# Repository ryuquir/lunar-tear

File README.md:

# Lunar Tear

Private server research project for a certain discontinued mobile game.
Discord server: https://discord.gg/G3anrfcV

## How To Launch The Server

### Prerequisites

- Go 1.24+
- Populated `server/assets/` directory

### Regenerate protobuf stubs

```bash
cd server
make proto
```

### Run

```bash
cd server
sudo go run ./cmd/lunar-tear \
  --host 10.0.2.2 \
  --http-port 8080 \
  --scene 13
```

`sudo` is needed because gRPC binds to port 443 (privileged). On Linux you can use `setcap` instead:

```bash
go build -o lunar-tear ./cmd/lunar-tear
sudo setcap cap_net_bind_service=+ep ./lunar-tear
./lunar-tear --host 10.0.2.2 --http-port 8080 --scene 13
```

### Ports

| Protocol | Port | Notes                                                |
| -------- | ---- | ---------------------------------------------------- |
| gRPC     | 443  | hardcoded by the client, not configurable            |
| HTTP     | 8080 | Octo asset API + game web pages (`--http-port` flag) |

### Flags

| Flag                   | Default             | Description                                              |
| ---------------------- | ------------------- | -------------------------------------------------------- |
| `--host`               | `127.0.0.1`         | hostname/IP given to the client                          |
| `--http-port`          | `8080`              | HTTP/Octo server port                                    |
| `--resources-base-url` | (derived from host) | base URL for list.bin rewrite (must be exactly 43 chars) |
| `--scene`              | `0`                 | bootstrap new users to scene N (0 = fresh start)         |

### `--resources-base-url`

Overrides the base URL the client uses to fetch resources. The replacement string **must be exactly 43 characters**. If omitted, the server derives it from `--host` and `--http-port` automatically (when the result happens to be 43 characters). If the length doesn't match, the server logs a warning and serves the resource list unchanged.

```bash
sudo go run ./cmd/lunar-tear \
  --host 10.0.2.2 \
  --http-port 8080 \
  --resources-base-url "http://192.168.1.50:8080/res-bundle-srv" \
  --scene 13
```

> **Tip:** verify the length with `printf "your-url-here" | wc -c`.

## ⚠️ Legal Disclaimer

**Lunar Tear** is a fan-made, non-commercial **preservation and research project** dedicated to keeping a certain discontinued mobile game playable for educational and archival purposes.

- This project is **not affiliated with**, **endorsed by**, or **approved by** the original publisher or any of its subsidiaries.
- All trademarks, copyrights, and intellectual property related to the original game and its associated franchises belong to their respective owners.
- All code in this repository is original work developed through clean-room reverse engineering for interoperability with the game client.
- No copyrighted game assets, binaries, or master data are distributed in this repository.

**Use at your own risk.** The author assumes no liability for any damages or legal consequences that may arise from using this software. By using or contributing to this project, you are solely responsible for ensuring your usage complies with all applicable laws in your jurisdiction.

This project is released under the [MIT License](LICENSE).

**If you are a rights holder with concerns regarding this project**, please contact me directly.

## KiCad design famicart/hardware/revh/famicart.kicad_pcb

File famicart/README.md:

# famicart — RP2040/RP2350 ファミコン・マルチマッパー・カートリッジ ファームウェア＋基板

ファミコン（NES）の公式・ライセンス品 2,233 タイトルで使われた 92 種のマッパーを調査し、その全種（タイトル数ベース **99.0%**（2,211 本）。残り 22 本はデータベース上の不良ダンプ）に加え、基板名の記録がない市販 FC ソフト用のマッパーも含めて計 98 種をソフトウェアで再現する 1 チップ・カートリッジのファームウェアです。フラッシュに書き込んだ ROM 画像からマッパーを自動判別し、プロファイル指定で「MMC5 のバンク機能 + VRC7 音源」のような拡張 IC の組み合わせも可能にします。

> **重要な前提**: Seeed Studio XIAO RP2040 は GPIO が 11 本しかなく、単体ではカートリッジバス（最低 26 本）を駆動できません。理由と数値は [docs/01_feasibility.md](docs/01_feasibility.md) を参照。そのため **rev C 基板では基板直付けの RP2350B（GPIO 48 本）がバスを担当し、XIAO RP2040 は拡張音源コプロセッサ**として同居します（[docs/04_hardware.md](docs/04_hardware.md) の rev C 節）。rev A/B は Pico / Pico 2 モジュール 1 個の構成です。

## 状態（フェーズ 1・2 完了、フェーズ 3 = 実機検証 待ち）

| 項目 | 状態 |
|---|---|
| マッパー調査・集計（Mesen DB 由来） | 完了 → [docs/03_mapper_coverage.md](docs/03_mapper_coverage.md) |
| コア（バンク表・マッパー 99 種〔ライセンス品の 98 種＋自作向けのマッパー 30（UNROM 512、フラッシュ自己書き込み対応）〕・ROM 判別・DB 2,840 件・プロファイル） | 実装済み、ホストテスト 2,122 チェック通過 |
| 拡張音源レジスタ・ルーター（組み合わせ機構） | 実装済み |
| 拡張音源の合成（VRC6/VRC7/MMC5/N163/5B/FDS、`src/core/audio/synth.c`） | 実装済み（6 音源とも発音をホストテストで確認、VRC7 は OPLL 近似）。rev C では XIAO 側で動作 |
| PIO バス・フロントエンド、2 コア処理、PWM 音声出力 | 実装済み・**実機未検証** |
| USB-CDC コマンド（INFO / RESET / BOOTSEL / LOAD / PROFILE）と転送ツール `tools/fcload.py` | 実装済み・**実機未検証** |
| Pico / Pico 2 / RP2350B / XIAO（コプロセッサ）向けビルド | 通過（Pico: text 120KB, BSS 249KB / RP2350B: text 106KB, BSS 512KB / XIAO audio: text 42KB） |
| 2 MCU 間 UART リンク（3 Mbaud、音源レジスタのストリーム） | 実装済み・**実機未検証** |
| 回路図・基板 rev B（Pico 2、KiCad 7、90×46.1 mm〔※外形は旧寸法で切り欠きなし＝基板単体用。[04](docs/04_hardware.md) の訂正を参照〕、USB-C・リセット付き、未接続 0・DRC 0）・ガーバー・JLCPCB 実装パッケージ | [hardware/](hardware/)、[hardware/jlcpcb/](hardware/jlcpcb/) |
| 回路図・基板 rev C（RP2350B + XIAO RP2040、USB 3 口、リセット端子 J2、未接続 0・DRC 0）・ガーバー・JLCPCB 実装パッケージ | [hardware/revc/](hardware/revc/) |
| 回路図・基板 rev D（**実機動作の本命**: 実カセット型分離構成、RP2350B×2 マッパーチップ + PRG/CHR パラレル NOR 64 MB×2 + F-RAM 128 KB + CHR SRAM 512 KB、**6 層、未接続 0・DRC エラー 0**、起動バンク付き）・ガーバー・JLCPCB 実装パッケージ | [hardware/revd/](hardware/revd/)、[hardware/revd/jlcpcb/](hardware/revd/jlcpcb/)、docs/04_hardware.md の rev D 節 |
| 回路図・基板 rev E（※外形は旧寸法で切り欠きなし＝基板単体用。標準シェルには Pico 2 が 1 枚しか入らないため rev E は標準シェル不可、[04 の訂正](docs/04_hardware.md)）（**実際に作れる安価な版**: Pico 2 ×2 + XIAO RP2350、JLCPCB Basic 部品のみ 10 種・45 点、2 層、未接続 0・DRC エラー 0、MMC5 完全対応の配線）・ガーバー・JLCPCB 実装パッケージ | [hardware/reve/](hardware/reve/)、[docs/06_rev_e_plan.md](docs/06_rev_e_plan.md) |
| 回路図・基板 **rev F2**（rev F の回路を**任天堂の大型シェル**に合わせ、4 資料から作った外形〔切り欠き・スリット・リブ回避。実物では未確認〕で配置、90 × 85.7 mm、Pico 2 ×4 + XIAO、Basic 部品のみ 10 種・54 点、2 層、**未接続 0・DRC エラー 0**） | [hardware/revf2/](hardware/revf2/)、[docs/10_rev_f_board.md](docs/10_rev_f_board.md) |
| 回路図・基板 **rev G**（Pico 2 ×2 ＋ XIAO RP2350 ×2 を基本に、増設 Pico 2 ×2〔512 KB 級の PRG・CHR 用、任意〕、16 MB フラッシュ、microSD〔任意〕。任天堂の大型シェル用 89.6 × 85.7 mm、2 層、Basic 部品のみ 10 種・81 点、**未接続 0・DRC エラー 0**。外形・ビア・シルク・端子部を JLCPCB の製造条件に合わせ、Standard PCBA 用の注文パッケージ（捨て基板を描き込んだデータと、基板だけのデータ）を付けた。検査ツールが 2 つのガーバー ZIP の中身と捨て基板の寸法をデータから測る。設計レビューで見つかった回路の問題〔書き込みストローブ、/ROMSEL、PPU /WE、31 番端子、PPU データ線の直列抵抗など〕を修正。**実機とシェルの実物では未検証、rev G 用のファームは未作成**） | [hardware/revg/](hardware/revg/)（[外形図](hardware/revg/outline.png)、[配置図](hardware/revg/placement.png)、[注文メモ](hardware/revg/jlcpcb/README.md)）、[docs/12_rev_g_plan.md](docs/12_rev_g_plan.md)、ファミコン本体の仕様と全端子は [docs/11_famicom_reference.md](docs/11_famicom_reference.md) |
| 回路図・基板 **rev H**（rev G の 6 つのモジュールを RP2350B 6 個の直接実装に置き換え、計算専用の RP2350B 2 個を足した計 8 個。**JLCPCB の実装だけで完成**する rev G の上位互換。各チップに 16 MB フラッシュ、チップ間の高速リンク、共通のコア電源、6 層・両面実装（表は受動部品だけ）・25 種 296 点、ファミコンの電源だけで動かすための電流の決まり。任天堂の大型シェル用、線幅と間隔 0.12 mm、**未接続 0・DRC エラー 0**、JLCPCB の注文パッケージと GrokBOT 用の注文手順付き。**ファームは未作成**） | [hardware/revh/](hardware/revh/)、[docs/13_rev_h_plan.md](docs/13_rev_h_plan.md) |
| 回路図・基板 rev F（rev E + SFC 型コプロセッサ用 Pico 2 ×2、90 × 70.1 mm、Basic 部品のみ 10 種・54 点、2 層、**未接続 0・DRC エラー 0**。外形は旧寸法で切り欠きなし＝基板単体用） | [hardware/revf/](hardware/revf/)、[docs/10_rev_f_board.md](docs/10_rev_f_board.md)、コプロセッサ ABI は [docs/09_coproc_abi.md](docs/09_coproc_abi.md) |
| rev E ファームウェア（U1 CPU バス応答・書き込み取り込み・CHR-RAM 再現・起動手順・ROM ライブラリ、U2 CHR/CIRAM /CE・MMC5 PPU 処理、U3 IRQ・拡張音源、3 台リンク） | 実装済み・3 本ともビルド通過、ホストテスト通過（rev E 分 52 項目、追加マッパー 524 項目）、**実機未検証**。[docs/07_rev_e_firmware.md](docs/07_rev_e_firmware.md) |
| rev D ファームウェア（バンク線出力、2 MCU リンク、外部フラッシュ書き込み、ROM ライブラリ、ブートスタブ） | 実装済み・ビルド通過（U1 text 130 KB / U2 37 KB）、ホストテスト通過、**実機未検証** |

## ビルド

```sh
# ホスト側ユニットテスト
cd famicart/test && make

# ファームウェア（FC_BOARD = pico | pico2 | rp2350b | xiao_audio | xiao_rp2040）
cd famicart && mkdir -p build && cd build
cmake -DPICO_SDK_PATH=/path/to/pico-sdk -DFC_BOARD=pico2 ..
make -j
# -> famicart.uf2 を BOOTSEL モードのドライブへコピー

# rev C 基板は 2 つ書く: 主 MCU（J3 を挿し SW2 を押しながら SW1 を離す）と XIAO（XIAO 自身の USB-C と BOOT ボタン）
cmake -S . -B build-rp2350b   -DFC_BOARD=rp2350b   && cmake --build build-rp2350b   # -> RP2350B へ
cmake -S . -B build-xiao_audio -DFC_BOARD=xiao_audio && cmake --build build-xiao_audio # -> XIAO RP2040 へ

# rev H の待機用プログラム（チップごと。FC_REVH_CHIP = 1〜6・8・9、6 はハブ。docs/13 の「ファームの土台」）
cmake -S . -B build-revh_u6 -DFC_BOARD=revh -DFC_REVH_CHIP=6 && cmake --build build-revh_u6   # ピンのヘッダーの確認: python3 tools/fw/gen_revh_pins.py --check
```

## ROM の書き込み（自動判別）

```sh
# そのまま: ヘッダ → CRC32 DB → サイズ推定 の順で自動判別
python3 tools/rom2uf2.py game.nes -o game.uf2 --family rp2350

# マッパーを強制し、VRC7 音源を追加（MMC5 の機能 + VRC7 の音）
python3 tools/rom2uf2.py game.nes -o game.uf2 --mapper 5 --audio vrc7:exclusive --audio mmc5

# レジスタ窓が衝突する組み合わせは窓を移動（VRC6 のレジスタを $C000 へ）
python3 tools/rom2uf2.py game.nes -o game.uf2 --audio vrc6@0xC000
```

## 本体に挿したまま ROM を転送（USB-C）

```sh
pip install pyserial
python3 tools/fcload.py /dev/ttyACM0 info          # 判別結果・バス統計
python3 tools/fcload.py /dev/ttyACM0 load game.nes # 転送 → カートリッジ自動再起動 → 本体のリセットを押す
python3 tools/fcload.py /dev/ttyACM0 reset         # ソフトからカートリッジをリセット
python3 tools/fcload.py /dev/ttyACM0 bootsel       # ファーム更新用 UF2 モードへ
```

ROM はフラッシュ先頭から 256KB の位置（`FC_FLASH_ROM_SLOT`）に、48 バイトのプロファイル（256 バイト境界にパディング）＋画像の形で書き込まれます。ツールを介さず `.nes` を直接その位置に焼いた場合もヘッダ/DB で判別します。起動後、USB CDC（115200）に判別結果とバス統計が 2 秒ごとに出ます。

## データベースの再生成

```sh
python3 tools/gen_romdb.py   # data/MesenNesDB.txt -> src/core/romdb_gen.h, docs/03_mapper_coverage.md
```

## ドキュメント

- [01 実現可能性](docs/01_feasibility.md) — ピン数・タイミング・メモリの数値と結論
- [02 ファームウェア構成](docs/02_architecture.md) — 高速パス、マッパー IF、音源ルーター、判別フロー、既知の制約
- [03 マッパー集計](docs/03_mapper_coverage.md) — 92 種の本数・サブマッパー・代表基板・実装状況
- [04 ハードウェア](docs/04_hardware.md) — KiCad プロジェクト、基板寸法、GPIO 割当、部品表、音声ミックス回路

## 基板の再生成（KiCad 7 + Freerouting）

```sh
cd famicart/tools/pcb
python3 gen_sch.py && python3 route_pcb.py && python3 gen_bom.py && python3 gen_jlc.py            # rev B -> hardware/
FC_DESIGN=design_revc FC_HW_DIR=../../hardware/revc python3 gen_sch.py   # rev C -> hardware/revc/（route_pcb / gen_bom / gen_jlc も同じ環境変数で）
FC_DESIGN=design_revd FC_HW_DIR=../../hardware/revd FC_LAYERS=6 FC_STUBS=1 FC_TRACK=0.1 FC_CLEAR=0.1 FC_VIA=0.5 FC_VIA_DRILL=0.2 python3 route_pcb.py   # rev D（6 層）
python3 finish_route.py ../../hardware/revd/famicart.kicad_pcb   # Freerouting が残した接続を仕上げる（その後 route_pcb.py export）
```

## ロードマップ

1. **フェーズ 3**: 基板の試作・実機検証（ロジアナでタイミング確認）、配線の手直し、VRC7 音色の実機比較による校正、USB マスストレージからの ROM 選択、セーブ（バッテリ RAM）のフラッシュ退避
2. **フェーズ 4（rev D 向けファーム）**: 実装済み（バンク出力・リンク・フラッシュ書き込み・ライブラリ・ブートスタブ）。残り: 起動メニュー（コントローラでライブラリ選択）、MMC5 $5204 状態の U2→U1 同期、$6000 PRG-ROM マッパーの F-RAM コピー対応
3. **フェーズ 5（実機ブリングアップ）**: 基板到着後 `FLASHID` → `BOOTBANK` → `libadd` NROM → MMC1 → MMC3 → MMC5 の順に確認。ロジアナで M2 ↔ バンク線・/RD ↔ CHR バンク線の遅延を測る
4. 未実装マッパー（海賊版マルチカート系）は対象外のまま

## ライセンス・出典

ファームウェアはリポジトリのライセンスに従います。`data/MesenNesDB.txt` は Mesen プロジェクト配布の生成データ（NesCartDB および NewRisingSun の NES 2.0 header database 由来）で、マッパー判別用のメタデータのみを利用しています。ゲーム ROM は含みません。

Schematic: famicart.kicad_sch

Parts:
C1, C2, C5, C6, C7, C9, C10, C11, C12, C13, C14, C16, C17, C18, C21, C22, C23, C24, C25, C26, C27, C28, C29, C30, C31, C33, C34, C35, C38, C39, C40, C41, C42, C43, C44, C45, C46, C47, C48, C50, C51, C52, C55, C56, C57, C58, C59, C60, C61, C62, C63, C64, C65, C67, C68, C69, C72, C73, C74, C75, C76, C77, C78, C79, C80, C81, C82, C84, C85, C86, C89, C90, C91, C92, C93, C94, C95, C96, C97, C98, C99, C101, C102, C103, C106, C107, C108, C109, C110, C111, C112, C113, C114, C115, C116, C118, C119, C120, C123, C124, C125, C126, C127, C128, C129, C130, C131, C132, C133, C135, C136, C137, C148: 100n; C_0402_1005Metric
C3, C4, C8, C142, C145, C146: 10u; C_0805_2012Metric
C15, C32, C49, C66, C83, C100, C117, C134, C147: 4.7u; C_0603_1608Metric
C19, C20, C36, C37, C53, C54, C70, C71, C87, C88, C104, C105, C121, C122, C138, C139: 12p; C_0402_1005Metric
C140, C141: 10n; C_0603_1608Metric
C143, C144: 22u; C_0805_2012Metric
D5, D6, D7, D8, D9: BAV99; SOT-23
D10, D11: B5819W; D_SOD-123
D21, D22, D23, D24, D25, D26, D28, D29: KT-0603R; LED_0603_1608Metric
J1: Famicom 60-pin edge; Famicom_CardEdge_60_M
J2: RST/GND/LINK pads; WirePads_1x3
J3: TF-01A; microSD_HRO_TF-01A
J4: EXT/GND/3V3 pads; WirePads_1x3
J5: hub SWD pads; PinHeader_1x05_P1.27mm_Vertical_SMD_Pin1Left
J6: SWD pads U1-U5 U8 U9; PinHeader_2x08_P1.27mm_Vertical_SMD
J7: TYPE-C-31-M-12; USB_C_Receptacle_HRO_TYPE-C-31-M-12_JLC
L1, L2: 2.2uH; L_SXN_SMNR4020
Q1, Q2, Q3, Q4, Q5, Q6, Q7: 2N7002; SOT-23
R1, R3, R5, R7, R9, R11, R13, R15, R52: 1k; R_0402_1005Metric
R2, R4, R6, R8, R10, R12, R14, R16, R17, R19, R20, R21, R22, R23, R24, R28, R29, R32, R37, R51, R54: 2.2k; R_0603_1608Metric
R18, R33, R34, R35, R46, R48, R49, R50: 100k; R_0603_1608Metric
R25, R26, R27, R30, R31, R36, R40, R41, R42, R43, R44, R45, R47, R53: 10k; R_0603_1608Metric
R38, R39: 27; R_0402_1005Metric
RN1, RN2, RN3, RN4, RN7, RN8, RN9, RN10, RN17, RN18, RN19, RN20, RN21, RN22, RN23, RN24, RN25, RN26, RN31, RN32: 1k x4; R_Array_Convex_4x0603
RN5, RN6, RN11, RN12, RN13, RN14, RN15, RN16, RN27, RN28, RN29, RN30: 680 x4; R_Array_Convex_4x0603
SW1: TS-1187A (RESET); SW_Push_1P1T_XKB_TS-1187A
SW2: TS-1187A (BOOTSEL); SW_Push_1P1T_XKB_TS-1187A
SW3: TS-1187A (HUB RUN); SW_Push_1P1T_XKB_TS-1187A
TP1: TP +1V1; TestPoint_Pad_1.5x1.5mm
TP2: TP +3V3; TestPoint_Pad_1.5x1.5mm
TP3: TP V5_IN; TestPoint_Pad_1.5x1.5mm
TP4: TP FB_3V3; TestPoint_Pad_1.5x1.5mm
TP5: TP FB_1V1; TestPoint_Pad_1.5x1.5mm
TP6: TP GND; TestPoint_Pad_1.5x1.5mm
U1, U2, U3, U4, U5, U6, U8, U9: RP2350B; QFN-80-1EP_10x10mm_P0.4mm_EP3.4x3.4mm_NoVia
U7, U11, U12, U13, U14, U15, U16, U18, U19: W25Q128JVSIQ; SOIC-8_5.23x5.23mm_P1.27mm
U20, U21: TLV62569DBVR; SOT-23-5
Y1, Y2, Y3, Y4, Y5, Y6, Y8, Y9: 12MHz; Crystal_SMD_3225-4Pin_3.2x2.5mm
ZA1, ZA2, ZA3, ZA4: 1k x4; R_Array_Convex_4x0603
ZD1, ZD2: 680 x4; R_Array_Convex_4x0603

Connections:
+1V1: C5.1, C10.1, C18.1, C23.1, C27.1, C35.1, C40.1, C44.1, C52.1, C57.1, C61.1, C69.1, C74.1, C78.1, C86.1, C91.1, C95.1, C103.1, C108.1, C112.1, C120.1, C125.1, C129.1, C137.1, C143.1, C144.1, L2.2, R30.1, TP1.1, U1.10 (DVDD), U1.32 (DVDD), U1.51 (DVDD), U2.10 (DVDD), U2.32 (DVDD), U2.51 (DVDD), U3.10 (DVDD), U3.32 (DVDD), U3.51 (DVDD), U4.10 (DVDD), U4.32 (DVDD), U4.51 (DVDD), U5.10 (DVDD), U5.32 (DVDD), U5.51 (DVDD), U6.10 (DVDD), U6.32 (DVDD), U6.51 (DVDD), U8.10 (DVDD), U8.32 (DVDD), U8.51 (DVDD), U9.10 (DVDD), U9.32 (DVDD), U9.51 (DVDD)
+3V3: C1.1, C2.1, C6.1, C7.1, C9.1, C11.1, C12.1, C13.1, C14.1, C15.1, C16.1, C17.1, C21.1, C22.1, C24.1, C25.1, C26.1, C28.1, C29.1, C30.1, C31.1, C32.1, C33.1, C34.1, C38.1, C39.1, C41.1, C42.1, C43.1, C45.1, C46.1, C47.1, C48.1, C49.1, C50.1, C51.1, C55.1, C56.1, C58.1, C59.1, C60.1, C62.1, C63.1, C64.1, C65.1, C66.1, C67.1, C68.1, C72.1, C73.1, C75.1, C76.1, C77.1, C79.1, C80.1, C81.1, C82.1, C83.1, C84.1, C85.1, C89.1, C90.1, C92.1, C93.1, C94.1, C96.1, C97.1, C98.1, C99.1, C100.1, C101.1, C102.1, C106.1, C107.1, C109.1, C110.1, C111.1, C113.1, C114.1, C115.1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
+5V: C3.1, C4.1, C8.1, D5.2 (A), D6.2 (A), D7.2 (A), D8.2 (A), D9.2 (A), D10.2 (A), J1.30 (+5V), J1.31 (CART_PRESENT), R17.2, R18.2, R26.1, RN18.5 (R4.2)
AF1: C140.1, RN19.3 (R3.1), RN19.5 (R4.2), RN19.8 (R1.2)
AF2: C141.1, RN19.2 (R2.1), RN19.6 (R3.2)
AMIX: R19.2, R20.1
AUDIO_IN: J1.45 (AUDIO_IN), R19.1
AUDIO_OUT: J1.46 (AUDIO_OUT), R20.2, RN19.7 (R2.2)
BOOT6: R52.2, SW2.1
CA0: RN1.8 (R1.2), U1.77 (GPIO0), U4.77 (GPIO0)
CA1: RN1.7 (R2.2), U1.78 (GPIO1), U4.78 (GPIO1)
CA2: RN1.6 (R3.2), U1.79 (GPIO2), U4.79 (GPIO2)
CA3: RN1.5 (R4.2), U1.80 (GPIO3), U4.80 (GPIO3)
CA4: RN2.8 (R1.2), U1.1 (GPIO4), U4.1 (GPIO4)
CA5: RN2.7 (R2.2), U1.2 (GPIO5), U4.2 (GPIO5)
CA6: RN2.6 (R3.2), U1.3 (GPIO6), U4.3 (GPIO6)
CA7: RN2.5 (R4.2), U1.4 (GPIO7), U4.4 (GPIO7)
CA8: RN3.8 (R1.2), U1.6 (GPIO8), U4.6 (GPIO8)
CA9: RN3.7 (R2.2), U1.7 (GPIO9), U4.7 (GPIO9)
CA10: RN3.6 (R3.2), U1.8 (GPIO10), U4.8 (GPIO10)
CA11: RN3.5 (R4.2), U1.9 (GPIO11), U4.9 (GPIO11)
CA12: RN4.6 (R3.2), U1.11 (GPIO12), U4.11 (GPIO12)
CA13: RN4.7 (R2.2), U1.12 (GPIO13), U4.12 (GPIO13)
CA14: RN4.8 (R1.2), U1.13 (GPIO14), U4.13 (GPIO14)
CC1: J7.A5 (CC1), R42.1, R43.1
CC2: J7.B5 (CC2), R40.1, R41.1
CD0: RN5.8 (R1.2), U1.14 (GPIO15)
CD1: RN5.7 (R2.2), U1.16 (GPIO16)
CD2: RN5.6 (R3.2), U1.17 (GPIO17)
CD3: RN5.5 (R4.2), U1.18 (GPIO18)
CD4: RN6.8 (R1.2), U1.19 (GPIO19)
CD5: RN6.7 (R2.2), U1.20 (GPIO20)
CD6: RN6.6 (R3.2), U1.21 (GPIO21)
CD7: RN6.5 (R4.2), U1.22 (GPIO22)
CIRAM_A10: J1.18 (CIRAM_A10), RN17.1 (R1.1), RN17.2 (R2.1)
CIRAM_nCE: J1.48 (CIRAM_~CE), R25.1, RN7.3 (R3.1), RN7.4 (R4.1)
CPU_A0: J1.13 (CPU_A0), RN1.1 (R1.1), ZA1.1 (R1.1)
CPU_A1: J1.12 (CPU_A1), RN1.2 (R2.1), ZA1.2 (R2.1)
CPU_A2: J1.11 (CPU_A2), RN1.3 (R3.1), ZA1.3 (R3.1)
CPU_A3: J1.10 (CPU_A3), RN1.4 (R4.1), ZA1.4 (R4.1)
CPU_A4: J1.9 (CPU_A4), RN2.1 (R1.1), ZA2.1 (R1.1)
CPU_A5: J1.8 (CPU_A5), RN2.2 (R2.1), ZA2.2 (R2.1)
CPU_A6: J1.7 (CPU_A6), RN2.3 (R3.1), ZA2.3 (R3.1)
CPU_A7: J1.6 (CPU_A7), RN2.4 (R4.1), ZA2.4 (R4.1)
CPU_A8: J1.5 (CPU_A8), RN3.1 (R1.1), ZA3.1 (R1.1)
CPU_A9: J1.4 (CPU_A9), RN3.2 (R2.1), ZA3.2 (R2.1)
CPU_A10: J1.3 (CPU_A10), RN3.3 (R3.1), ZA3.3 (R3.1)
CPU_A11: J1.2 (CPU_A11), RN3.4 (R4.1), ZA3.4 (R4.1)
CPU_A12: J1.33 (CPU_A12), RN4.3 (R3.1), ZA4.3 (R3.1)
CPU_A13: J1.34 (CPU_A13), RN4.2 (R2.1), ZA4.2 (R2.1)
CPU_A14: J1.35 (CPU_A14), RN4.1 (R1.1), ZA4.1 (R1.1)
CPU_D0: J1.43 (CPU_D0), RN5.1 (R1.1), RN13.1 (R1.1), ZD1.1 (R1.1)
CPU_D1: J1.42 (CPU_D1), RN5.2 (R2.1), RN13.2 (R2.1), ZD1.2 (R2.1)
CPU_D2: J1.41 (CPU_D2), RN5.3 (R3.1), RN13.3 (R3.1), ZD1.3 (R3.1)
CPU_D3: J1.40 (CPU_D3), RN5.4 (R4.1), RN13.4 (R4.1), ZD1.4 (R4.1)
CPU_D4: J1.39 (CPU_D4), RN6.1 (R1.1), RN14.1 (R1.1), ZD2.1 (R1.1)
CPU_D5: J1.38 (CPU_D5), RN6.2 (R2.1), RN14.2 (R2.1), ZD2.2 (R2.1)
CPU_D6: J1.37 (CPU_D6), RN6.3 (R3.1), RN14.3 (R3.1), ZD2.3 (R3.1)
CPU_D7: J1.36 (CPU_D7), RN6.4 (R4.1), RN14.4 (R4.1), ZD2.4 (R4.1)
CPU_RW: D6.3 (K), J1.14 (CPU_R/~W), Q2.1 (G), R18.1, RN31.2 (R2.1), RN31.4 (R4.1)
C_M2: RN4.5 (R4.2), U1.25 (GPIO24), U4.25 (GPIO24)
C_ROMSEL: RN31.6 (R3.2), U1.26 (GPIO25), U4.26 (GPIO25)
C_RW: RN31.5 (R4.2), U1.23 (GPIO23), U4.23 (GPIO23)
EXT: R54.2, U6.52 (GPIO41_ADC1)
EXT_P: J4.1, R54.1
FB_1V1: R30.2, R31.1, R33.1, TP5.1, U21.5 (FB)
FB_1V1_M: R31.2, R32.1
FB_3V3: R36.2, R37.1, TP4.1, U20.5 (FB)
GND: C1.2, C2.2, C3.2, C4.2, C5.2, C6.2, C7.2, C8.2, C9.2, C10.2, C11.2, C12.2, C13.2, C14.2, C15.2, C16.2, C17.2, C18.2, C19.2, C20.2, C21.2, C22.2, C23.2, C24.2, C25.2, C26.2, C27.2, C28.2, C29.2, C30.2, C31.2, C32.2, C33.2, C34.2, C35.2, C36.2, C37.2, C38.2, C39.2, C40.2, C41.2, C42.2, C43.2, C44.2, C45.2, C46.2, C47.2, C48.2, C49.2, C50.2, C51.2, C52.2, C53.2, C54.2, C55.2, C56.2, C57.2, C58.2, C59.2, C60.2, C61.2, C62.2, C63.2, C64.2, C65.2, C66.2, C67.2, C68.2, C69.2, C70.2, C71.2, C72.2, C73.2, C74.2, C75.2, C76.2, C77.2, C78.2, C79.2, C80.2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
HIRQ: U3.39 (GPIO31), U6.40 (GPIO32)
HM2: RN18.8 (R1.2), U6.42 (GPIO33)
IRQ4: U3.53 (GPIO42_ADC2), U4.55 (GPIO44_ADC4)
IRQ5: U3.54 (GPIO43_ADC3), U5.55 (GPIO44_ADC4)
IRQ_G: Q5.1 (G), R21.1, U3.38 (GPIO30)
LED1: R8.1, U1.58 (GPIO47_ADC7)
LED1_A: D21.2 (A), R8.2
LED2: R4.1, U2.56 (GPIO45_ADC5)
LED2_A: D22.2 (A), R4.2
LED3: R6.1, U3.56 (GPIO45_ADC5)
LED3_A: D23.2 (A), R6.2
LED4: R16.1, U4.57 (GPIO46_ADC6)
LED4_A: D24.2 (A), R16.2
LED5: R12.1, U5.57 (GPIO46_ADC6)
LED5_A: D25.2 (A), R12.2
LED6: R14.1, U6.48 (GPIO39)
LED6_A: D26.2 (A), R14.2
LED8: R10.1, U8.56 (GPIO45_ADC5)
LED8_A: D28.2 (A), R10.2
LED9: R2.1, U9.56 (GPIO45_ADC5)
LED9_A: D29.2 (A), R2.2
LINK: R22.1, R24.1, RN20.5 (R4.2), RN20.6 (R3.2), RN20.7 (R2.2), RN20.8 (R1.2), RN21.5 (R4.2), RN21.6 (R3.2), RN21.7 (R2.2), RN21.8 (R1.2), RN22.5 (R4.2), RN22.6 (R3.2), RN22.7 (R2.2), RN22.8 (R1.2), RN23.5 (R4.2), RN23.6 (R3.2), RN23.7 (R2.2), RN23.8 (R1.2), RN24.5 (R4.2), RN24.6 (R3.2), RN24.7 (R2.2), RN24.8 (R1.2), RN25.5 (R4.2), RN25.6 (R3.2), RN25.7 (R2.2), RN25.8 (R1.2)
LINK_A: RN20.1 (R1.1), RN20.2 (R2.1), RN20.3 (R3.1), RN20.4 (R4.1), U1.36 (GPIO28)
LINK_B: RN22.1 (R1.1), RN22.2 (R2.1), RN22.3 (R3.1), RN22.4 (R4.1), U2.36 (GPIO28)
LINK_C: RN24.1 (R1.1), RN24.2 (R2.1), RN24.3 (R3.1), RN24.4 (R4.1), U3.36 (GPIO28)
LINK_D: RN21.1 (R1.1), RN21.2 (R2.1), RN21.3 (R3.1), RN21.4 (R4.1), U4.36 (GPIO28)
LINK_E: RN23.1 (R1.1), RN23.2 (R2.1), RN23.3 (R3.1), RN23.4 (R4.1), U5.36 (GPIO28)
LINK_F: RN25.1 (R1.1), RN25.2 (R2.1), RN25.3 (R3.1), RN25.4 (R4.1), U6.77 (GPIO0)
LINK_PU: R22.2, R23.1
LINK_T: J2.3, R24.2
M2: D5.3 (K), J1.32 (M2), Q1.1 (G), RN4.4 (R4.1), RN18.1 (R1.1), ZA4.4 (R4.1)
M2n: Q1.3 (D), Q3.1 (G), RN18.4 (R4.1)
NA10_D: RN17.7 (R2.2), RN17.8 (R1.2), U3.47 (GPIO38)
NCE_D: RN7.5 (R4.2), RN7.6 (R3.2), U3.46 (GPIO37)
PA0: RN10.6 (R3.2), U2.77 (GPIO0), U5.77 (GPIO0)
PA1: RN9.8 (R1.2), U2.78 (GPIO1), U5.78 (GPIO1)
PA2: RN9.6 (R3.2), U2.79 (GPIO2), U5.79 (GPIO2)
PA3: RN8.8 (R1.2), U2.80 (GPIO3), U5.80 (GPIO3)
PA4: RN8.6 (R3.2), U2.1 (GPIO4), U5.1 (GPIO4)
PA5: RN7.8 (R1.2), U2.2 (GPIO5), U5.2 (GPIO5)
PA6: RN7.7 (R2.2), U2.3 (GPIO6), U5.3 (GPIO6)
PA7: RN8.5 (R4.2), U2.4 (GPIO7), U5.4 (GPIO7)
PA8: RN8.7 (R2.2), U2.6 (GPIO8), U5.6 (GPIO8)
PA9: RN9.5 (R4.2), U2.7 (GPIO9), U5.7 (GPIO9)
PA10: RN9.7 (R2.2), U2.8 (GPIO10), U3.40 (GPIO32), U5.8 (GPIO10)
PA11: RN10.5 (R4.2), U2.9 (GPIO11), U3.42 (GPIO33), U5.9 (GPIO11)
PA12: RN10.7 (R2.2), U2.11 (GPIO12), U3.43 (GPIO34), U5.11 (GPIO12)
PA13: RN10.8 (R1.2), U2.12 (GPIO13), U3.44 (GPIO35), U5.12 (GPIO13)
PD0: RN11.5 (R4.2), RN11.6 (R3.2), U2.13 (GPIO14)
PD1: RN11.7 (R2.2), RN11.8 (R1.2), U2.14 (GPIO15)
PD2: RN12.5 (R4.2), RN12.6 (R3.2), U2.16 (GPIO16)
PD3: RN12.7 (R2.2), RN12.8 (R1.2), U2.17 (GPIO17)
PD4: RN16.5 (R4.2), RN16.6 (R3.2), U2.18 (GPIO18)
PD5: RN16.7 (R2.2), RN16.8 (R1.2), U2.19 (GPIO19)
PD6: RN15.5 (R4.2), RN15.6 (R3.2), U2.20 (GPIO20)
PD7: RN15.7 (R2.2), RN15.8 (R1.2), U2.21 (GPIO21)
PEV: U2.23 (GPIO23), U3.48 (GPIO39)
PLINK_B: RN26.7 (R2.2), RN26.8 (R1.2), U2.28 (GPIO27)
PLINK_E: RN26.5 (R4.2), RN26.6 (R3.2), U5.28 (GPIO27)
PLINK_F: RN26.1 (R1.1), RN26.2 (R2.1), RN26.3 (R3.1), RN26.4 (R4.1), U6.17 (GPIO17)
PPU_A0: J1.25 (PPU_A0), RN10.3 (R3.1)
PPU_A1: J1.24 (PPU_A1), RN9.1 (R1.1)
PPU_A2: J1.23 (PPU_A2), RN9.3 (R3.1)
PPU_A3: J1.22 (PPU_A3), RN8.1 (R1.1)
PPU_A4: J1.21 (PPU_A4), RN8.3 (R3.1)
PPU_A5: J1.20 (PPU_A5), RN7.1 (R1.1)
PPU_A6: J1.19 (PPU_A6), RN7.2 (R2.1)
PPU_A7: J1.50 (PPU_A7), RN8.4 (R4.1)
PPU_A8: J1.51 (PPU_A8), RN8.2 (R2.1)
PPU_A9: J1.52 (PPU_A9), RN9.4 (R4.1)
PPU_A10: J1.53 (PPU_A10), RN9.2 (R2.1)
PPU_A11: J1.54 (PPU_A11), RN10.4 (R4.1)
PPU_A12: J1.55 (PPU_A12), RN10.2 (R2.1)
PPU_A13: J1.56 (PPU_A13), RN10.1 (R1.1)
PPU_D0: J1.26 (PPU_D0), RN11.3 (R3.1), RN11.4 (R4.1), RN27.1 (R1.1), RN27.2 (R2.1)
PPU_D1: J1.27 (PPU_D1), RN11.1 (R1.1), RN11.2 (R2.1), RN27.3 (R3.1), RN27.4 (R4.1)
PPU_D2: J1.28 (PPU_D2), RN12.3 (R3.1), RN12.4 (R4.1), RN28.1 (R1.1), RN28.2 (R2.1)
PPU_D3: J1.29 (PPU_D3), RN12.1 (R1.1), RN12.2 (R2.1), RN28.3 (R3.1), RN28.4 (R4.1)
PPU_D4: J1.60 (PPU_D4), RN16.3 (R3.1), RN16.4 (R4.1), RN30.1 (R1.1), RN30.2 (R2.1)
PPU_D5: J1.59 (PPU_D5), RN16.1 (R1.1), RN16.2 (R2.1), RN30.3 (R3.1), RN30.4 (R4.1)
PPU_D6: J1.58 (PPU_D6), RN15.3 (R3.1), RN15.4 (R4.1), RN29.1 (R1.1), RN29.2 (R2.1)
PPU_D7: J1.57 (PPU_D7), RN15.1 (R1.1), RN15.2 (R2.1), RN29.3 (R3.1), RN29.4 (R4.1)
PPU_nRD: J1.17 (PPU_~RD), RN17.4 (R4.1), RN32.3 (R3.1)
PPU_nWE: J1.47 (PPU_~WR), RN17.3 (R3.1), RN32.4 (R4.1)
PWE_G: D9.3 (K), Q6.1 (G), RN17.6 (R3.2)
PWM: RN19.4 (R4.1), U3.37 (GPIO29)
PWM2: RN19.1 (R1.1), U6.43 (GPIO34)
PWS_D: Q6.3 (D), R28.1, R29.1, U2.27 (GPIO26), U5.27 (GPIO26)
P_WE: RN32.5 (R4.2), U2.25 (GPIO24), U5.25 (GPIO24)
QSPI1_SCLK: U1.71 (QSPI_SCLK), U11.6 (CLK)
QSPI1_SD0: U1.72 (QSPI_SD0), U11.5 (DI(IO0))
QSPI1_SD1: U1.74 (QSPI_SD1), U11.2 (DO(IO1))
QSPI1_SD2: U1.73 (QSPI_SD2), U11.3 (IO2)
QSPI1_SD3: U1.70 (QSPI_SD3), U11.7 (IO3)
QSPI1_SS: U1.75 (QSPI_SS), U11.1 (~CS)
QSPI2_SCLK: U2.71 (QSPI_SCLK), U12.6 (CLK)
QSPI2_SD0: U2.72 (QSPI_SD0), U12.5 (DI(IO0))
QSPI2_SD1: U2.74 (QSPI_SD1), U12.2 (DO(IO1))
QSPI2_SD2: U2.73 (QSPI_SD2), U12.3 (IO2)
QSPI2_SD3: U2.70 (QSPI_SD3), U12.7 (IO3)
QSPI2_SS: U2.75 (QSPI_SS), U12.1 (~CS)
QSPI3_SCLK: U3.71 (QSPI_SCLK), U13.6 (CLK)
QSPI3_SD0: U3.72 (QSPI_SD0), U13.5 (DI(IO0))
QSPI3_SD1: U3.74 (QSPI_SD1), U13.2 (DO(IO1))
QSPI3_SD2: U3.73 (QSPI_SD2), U13.3 (IO2)
QSPI3_SD3: U3.70 (QSPI_SD3), U13.7 (IO3)
QSPI3_SS: U3.75 (QSPI_SS), U13.1 (~CS)
QSPI4_SCLK: U4.71 (QSPI_SCLK), U14.6 (CLK)
QSPI4_SD0: U4.72 (QSPI_SD0), U14.5 (DI(IO0))
QSPI4_SD1: U4.74 (QSPI_SD1), U14.2 (DO(IO1))
QSPI4_SD2: U4.73 (QSPI_SD2), U14.3 (IO2)
QSPI4_SD3: U4.70 (QSPI_SD3), U14.7 (IO3)
QSPI4_SS: U4.75 (QSPI_SS), U14.1 (~CS)
QSPI5_SCLK: U5.71 (QSPI_SCLK), U15.6 (CLK)
QSPI5_SD0: U5.72 (QSPI_SD0), U15.5 (DI(IO0))
QSPI5_SD1: U5.74 (QSPI_SD1), U15.2 (DO(IO1))
QSPI5_SD2: U5.73 (QSPI_SD2), U15.3 (IO2)
QSPI5_SD3: U5.70 (QSPI_SD3), U15.7 (IO3)
QSPI5_SS: U5.75 (QSPI_SS), U15.1 (~CS)
QSPI6_SCLK: U6.71 (QSPI_SCLK), U7.6 (CLK), U16.6 (CLK)
QSPI6_SD0: U6.72 (QSPI_SD0), U7.5 (DI(IO0)), U16.5 (DI(IO0))
QSPI6_SD1: U6.74 (QSPI_SD1), U7.2 (DO(IO1)), U16.2 (DO(IO1))
QSPI6_SD2: U6.73 (QSPI_SD2), U7.3 (IO2), U16.3 (IO2)
QSPI6_SD3: U6.70 (QSPI_SD3), U7.7 (IO3), U16.7 (IO3)
QSPI6_SS: R52.1, U6.75 (QSPI_SS), U16.1 (~CS)
QSPI6_SS1: R51.1, U6.58 (GPIO47_ADC7), U7.1 (~CS)
QSPI8_SCLK: U8.71 (QSPI_SCLK), U18.6 (CLK)
QSPI8_SD0: U8.72 (QSPI_SD0), U18.5 (DI(IO0))
QSPI8_SD1: U8.74 (QSPI_SD1), U18.2 (DO(IO1))
QSPI8_SD2: U8.73 (QSPI_SD2), U18.3 (IO2)
QSPI8_SD3: U8.70 (QSPI_SD3), U18.7 (IO3)
QSPI8_SS: U8.75 (QSPI_SS), U18.1 (~CS)
QSPI9_SCLK: U9.71 (QSPI_SCLK), U19.6 (CLK)
QSPI9_SD0: U9.72 (QSPI_SD0), U19.5 (DI(IO0))
QSPI9_SD1: U9.74 (QSPI_SD1), U19.2 (DO(IO1))
QSPI9_SD2: U9.73 (QSPI_SD2), U19.3 (IO2)
QSPI9_SD3: U9.70 (QSPI_SD3), U19.7 (IO3)
QSPI9_SS: U9.75 (QSPI_SS), U19.1 (~CS)
RD_D: RN17.5 (R4.2), U2.22 (GPIO22), U5.22 (GPIO22)
RD_D3: RN32.6 (R3.2), U3.45 (GPIO36)
RSEL_D: Q4.3 (D), RN18.2 (R2.1), U1.27 (GPIO26), U4.27 (GPIO26)
RUN6: J5.3, SW3.1, U6.35 (RUN)
SD_CD: J3.9 (DET), U6.78 (GPIO1)
SD_CLK: J3.5 (CLK), U6.79 (GPIO2)
SD_CMD: J3.3 (CMD), R48.1, U6.80 (GPIO3)
SD_DAT0: J3.7 (DAT0), R49.1, U6.1 (GPIO4)
SD_DAT1: J3.8 (DAT1), R50.1, U6.2 (GPIO5)
SD_DAT2: J3.1 (DAT2), R46.1, U6.3 (GPIO6)
SD_DAT3: J3.2 (DAT3/CD), R47.1, U6.4 (GPIO7)
SWCLK1: J6.1, U1.33 (SWCLK), U6.46 (GPIO37)
SWCLK2: J6.3, U2.33 (SWCLK), U6.20 (GPIO20)
SWCLK3: J6.5, U3.33 (SWCLK), U6.22 (GPIO22)
SWCLK4: J6.7, U4.33 (SWCLK), U6.44 (GPIO35)
SWCLK5: J6.9, U5.33 (SWCLK), U6.18 (GPIO18)
SWCLK6: J5.1, U6.33 (SWCLK)
SWCLK8: J6.11, U6.54 (GPIO43_ADC3), U8.33 (SWCLK)
SWCLK9: J6.13, U6.56 (GPIO45_ADC5), U9.33 (SWCLK)
SWDIO1: J6.2, U1.34 (SWDIO), U6.47 (GPIO38)
SWDIO2: J6.4, U2.34 (SWDIO), U6.21 (GPIO21)
SWDIO3: J6.6, U3.34 (SWDIO), U6.23 (GPIO23)
SWDIO4: J6.8, U4.34 (SWDIO), U6.45 (GPIO36)
SWDIO5: J6.10, U5.34 (SWDIO), U6.19 (GPIO19)
SWDIO6: J5.2, U6.34 (SWDIO)
SWDIO8: J6.12, U6.55 (GPIO44_ADC4), U8.34 (SWDIO)
SWDIO9: J6.14, U6.57 (GPIO46_ADC6), U9.34 (SWDIO)
SW_1V1: L2.1, U21.3 (SW)
SW_3V3: L1.1, U20.3 (SW)
USB_DM: J7.A7 (D-), J7.B7 (D-), R39.2
USB_DM_R: R39.1, U6.66 (USB_DM)
USB_DP: J7.A6 (D+), J7.B6 (D+), R38.2
USB_DP_R: R38.1, U6.67 (USB_DP)
V5S: R26.2, R27.1, U6.49 (GPIO40_ADC0)
V5_IN: C142.1, C145.1, D10.1 (K), D11.1 (K), TP3.1, U20.1 (EN), U20.4 (VIN), U21.1 (EN), U21.4 (VIN)
VBUS: D11.2 (A), J7.A4 (VBUS), J7.A9 (VBUS), J7.B4 (VBUS), J7.B9 (VBUS), R44.1
VBUS_S: R44.2, R45.1, U6.53 (GPIO42_ADC2)
VSEL_D: Q7.3 (D), R34.2
VSEL_M: R33.2, R34.1
VSEL_S: Q7.1 (G), R35.1, U1.57 (GPIO46_ADC6), U2.55 (GPIO44_ADC4), U3.55 (GPIO44_ADC4), U4.56 (GPIO45_ADC5), U5.56 (GPIO45_ADC5), U6.26 (GPIO25), U8.55 (GPIO44_ADC4), U9.55 (GPIO44_ADC4)
WL_CK: U1.37 (GPIO29), U2.37 (GPIO29), U5.37 (GPIO29), U6.6 (GPIO8)
WL_D0: U1.38 (GPIO30), U2.38 (GPIO30), U5.38 (GPIO30), U6.7 (GPIO9)
WL_D1: U1.39 (GPIO31), U2.39 (GPIO31), U5.39 (GPIO31), U6.8 (GPIO10)
WS_D: Q2.3 (D), Q3.3 (D), RN18.3 (R3.1), U1.28 (GPIO27), U4.28 (GPIO27)
X14_1_CK: U1.47 (GPIO38), U4.52 (GPIO41_ADC1)
X14_1_D0: U1.48 (GPIO39), U4.53 (GPIO42_ADC2)
X14_1_D1: U1.49 (GPIO40_ADC0), U4.54 (GPIO43_ADC3)
X14_4_CK: U1.52 (GPIO41_ADC1), U4.47 (GPIO38)
X14_4_D0: U1.53 (GPIO42_ADC2), U4.48 (GPIO39)
X14_4_D1: U1.54 (GPIO43_ADC3), U4.49 (GPIO40_ADC0)
X25_2_CK: U2.47 (GPIO38), U5.52 (GPIO41_ADC1)
X25_2_D0: U2.48 (GPIO39), U5.53 (GPIO42_ADC2)
X25_2_D1: U2.49 (GPIO40_ADC0), U5.54 (GPIO43_ADC3)
X25_5_CK: U2.52 (GPIO41_ADC1), U5.47 (GPIO38)
X25_5_D0: U2.53 (GPIO42_ADC2), U5.48 (GPIO39)
X25_5_D1: U2.54 (GPIO43_ADC3), U5.49 (GPIO40_ADC0)
X48_4_CK: U4.40 (GPIO32), U8.44 (GPIO35)
X48_4_D0: U4.42 (GPIO33), U8.45 (GPIO36)
X48_4_D1: U4.43 (GPIO34), U8.46 (GPIO37)
X48_8_CK: U4.44 (GPIO35), U8.40 (GPIO32)
X48_8_D0: U4.45 (GPIO36), U8.42 (GPIO33)
X48_8_D1: U4.46 (GPIO37), U8.43 (GPIO34)
X59_5_CK: U5.40 (GPIO32), U9.44 (GPIO35)
X59_5_D0: U5.42 (GPIO33), U9.45 (GPIO36)
X59_5_D1: U5.43 (GPIO34), U9.46 (GPIO37)
X59_9_CK: U5.44 (GPIO35), U9.40 (GPIO32)
X59_9_D0: U5.45 (GPIO36), U9.42 (GPIO33)
X59_9_D1: U5.46 (GPIO37), U9.43 (GPIO34)
X89_8_CK: U8.47 (GPIO38), U9.52 (GPIO41_ADC1)
X89_8_D0: U8.48 (GPIO39), U9.53 (GPIO42_ADC2)
X89_8_D1: U8.49 (GPIO40_ADC0), U9.54 (GPIO43_ADC3)
X89_9_CK: U8.52 (GPIO41_ADC1), U9.47 (GPIO38)
X89_9_D0: U8.53 (GPIO42_ADC2), U9.48 (GPIO39)
X89_9_D1: U8.54 (GPIO43_ADC3), U9.49 (GPIO40_ADC0)
XD0: RN13.8 (R1.2), U4.14 (GPIO15)
XD1: RN13.7 (R2.2), U4.16 (GPIO16)
XD2: RN13.6 (R3.2), U4.17 (GPIO17)
XD3: RN13.5 (R4.2), U4.18 (GPIO18)
XD4: RN14.8 (R1.2), U4.19 (GPIO19)
XD5: RN14.7 (R2.2), U4.20 (GPIO20)
XD6: RN14.6 (R3.2), U4.21 (GPIO21)
XD7: RN14.5 (R4.2), U4.22 (GPIO22)
XH1_1_CK: U1.40 (GPIO32), U6.27 (GPIO26)
XH1_1_D0: U1.42 (GPIO33), U6.28 (GPIO27)
XH1_1_D1: U1.43 (GPIO34), U6.36 (GPIO28)
XH1_H_CK: U1.44 (GPIO35), U6.37 (GPIO29)
XH1_H_D0: U1.45 (GPIO36), U6.38 (GPIO30)
XH1_H_D1: U1.46 (GPIO37), U6.39 (GPIO31)
XH2_2_CK: U2.40 (GPIO32), U6.9 (GPIO11)
XH2_2_D0: U2.42 (GPIO33), U6.11 (GPIO12)
XH2_2_D1: U2.43 (GPIO34), U6.12 (GPIO13)
XH2_H_CK: U2.44 (GPIO35), U6.13 (GPIO14)
XH2_H_D0: U2.45 (GPIO36), U6.14 (GPIO15)
XH2_H_D1: U2.46 (GPIO37), U6.16 (GPIO16)
XIN1: C70.1, U1.30 (XIN), Y1.1
XIN2: C36.1, U2.30 (XIN), Y2.1
XIN3: C53.1, U3.30 (XIN), Y3.1
XIN4: C138.1, U4.30 (XIN), Y4.1
XIN5: C104.1, U5.30 (XIN), Y5.1
XIN6: C121.1, U6.30 (XIN), Y6.1
XIN8: C87.1, U8.30 (XIN), Y8.1
XIN9: C19.1, U9.30 (XIN), Y9.1
XOUT1: R7.1, U1.31 (XOUT)
XOUT1_R: C71.1, R7.2, Y1.3
XOUT2: R3.1, U2.31 (XOUT)
XOUT2_R: C37.1, R3.2, Y2.3
XOUT3: R5.1, U3.31 (XOUT)
XOUT3_R: C54.1, R5.2, Y3.3
XOUT4: R15.1, U4.31 (XOUT)
XOUT4_R: C139.1, R15.2, Y4.3
XOUT5: R11.1, U5.31 (XOUT)
XOUT5_R: C105.1, R11.2, Y5.3
XOUT6: R13.1, U6.31 (XOUT)
XOUT6_R: C122.1, R13.2, Y6.3
XOUT8: R9.1, U8.31 (XOUT)
XOUT8_R: C88.1, R9.2, Y8.3
XOUT9: R1.1, U9.31 (XOUT)
XOUT9_R: C20.1, R1.2, Y9.3
XSTAT0: U1.55 (GPIO44_ADC4), U3.49 (GPIO40_ADC0)
XSTAT1: U1.56 (GPIO45_ADC5), U3.52 (GPIO41_ADC1)
YD0: RN27.7 (R2.2), RN27.8 (R1.2), U5.13 (GPIO14)
YD1: RN27.5 (R4.2), RN27.6 (R3.2), U5.14 (GPIO15)
YD2: RN28.7 (R2.2), RN28.8 (R1.2), U5.16 (GPIO16)
YD3: RN28.5 (R4.2), RN28.6 (R3.2), U5.17 (GPIO17)
YD4: RN30.7 (R2.2), RN30.8 (R1.2), U5.18 (GPIO18)
YD5: RN30.5 (R4.2), RN30.6 (R3.2), U5.19 (GPIO19)
YD6: RN29.7 (R2.2), RN29.8 (R1.2), U5.20 (GPIO20)
YD7: RN29.5 (R4.2), RN29.6 (R3.2), U5.21 (GPIO21)
ZA0: U3.77 (GPIO0), ZA1.8 (R1.2)
ZA1: U3.78 (GPIO1), ZA1.7 (R2.2)
ZA2: U3.79 (GPIO2), ZA1.6 (R3.2)
ZA3: U3.80 (GPIO3), ZA1.5 (R4.2)
ZA4: U3.1 (GPIO4), ZA2.8 (R1.2)
ZA5: U3.2 (GPIO5), ZA2.7 (R2.2)
ZA6: U3.3 (GPIO6), ZA2.6 (R3.2)
ZA7: U3.4 (GPIO7), ZA2.5 (R4.2)
ZA8: U3.6 (GPIO8), ZA3.8 (R1.2)
ZA9: U3.7 (GPIO9), ZA3.7 (R2.2)
ZA10: U3.8 (GPIO10), ZA3.6 (R3.2)
ZA11: U3.9 (GPIO11), ZA3.5 (R4.2)
ZA12: U3.11 (GPIO12), ZA4.6 (R3.2)
ZA13: U3.12 (GPIO13), ZA4.7 (R2.2)
ZA14: U3.13 (GPIO14), ZA4.8 (R1.2)
ZD0: U3.14 (GPIO15), ZD1.8 (R1.2)
ZD1: U3.16 (GPIO16), ZD1.7 (R2.2)
ZD2: U3.17 (GPIO17), ZD1.6 (R3.2)
ZD3: U3.18 (GPIO18), ZD1.5 (R4.2)
ZD4: U3.19 (GPIO19), ZD2.8 (R1.2)
ZD5: U3.20 (GPIO20), ZD2.7 (R2.2)
ZD6: U3.21 (GPIO21), ZD2.6 (R3.2)
ZD7: U3.22 (GPIO22), ZD2.5 (R4.2)
ZM2: U3.23 (GPIO23), ZA4.5 (R4.2)
Z_ROMSEL: RN31.8 (R1.2), U3.26 (GPIO25)
Z_RW: RN31.7 (R2.2), U3.25 (GPIO24)
nIRQ: D8.3 (K), J1.15 (~IRQ), Q5.3 (D)
nROMSEL: D7.3 (K), J1.44 (~ROMSEL), Q4.1 (G), R17.1, RN31.1 (R1.1), RN31.3 (R3.1)
nRST: J2.1, R53.1, SW1.1, U1.35 (RUN), U2.35 (RUN), U3.35 (RUN), U4.35 (RUN), U5.35 (RUN), U6.25 (GPIO24), U8.35 (RUN), U9.35 (RUN)

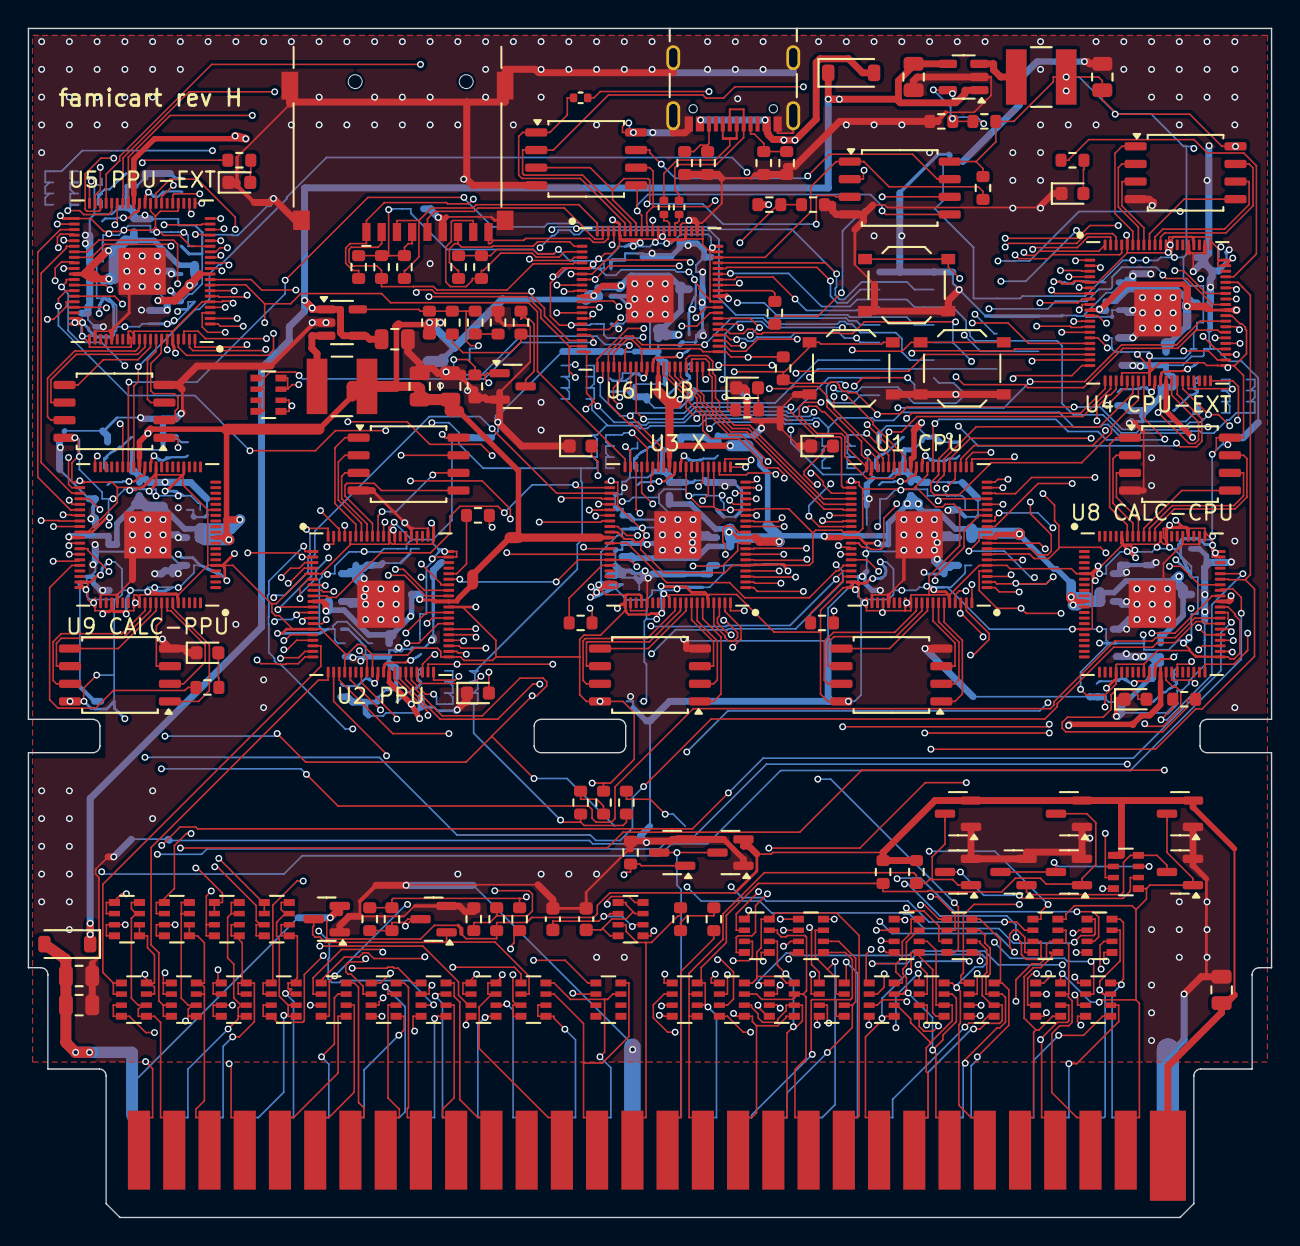
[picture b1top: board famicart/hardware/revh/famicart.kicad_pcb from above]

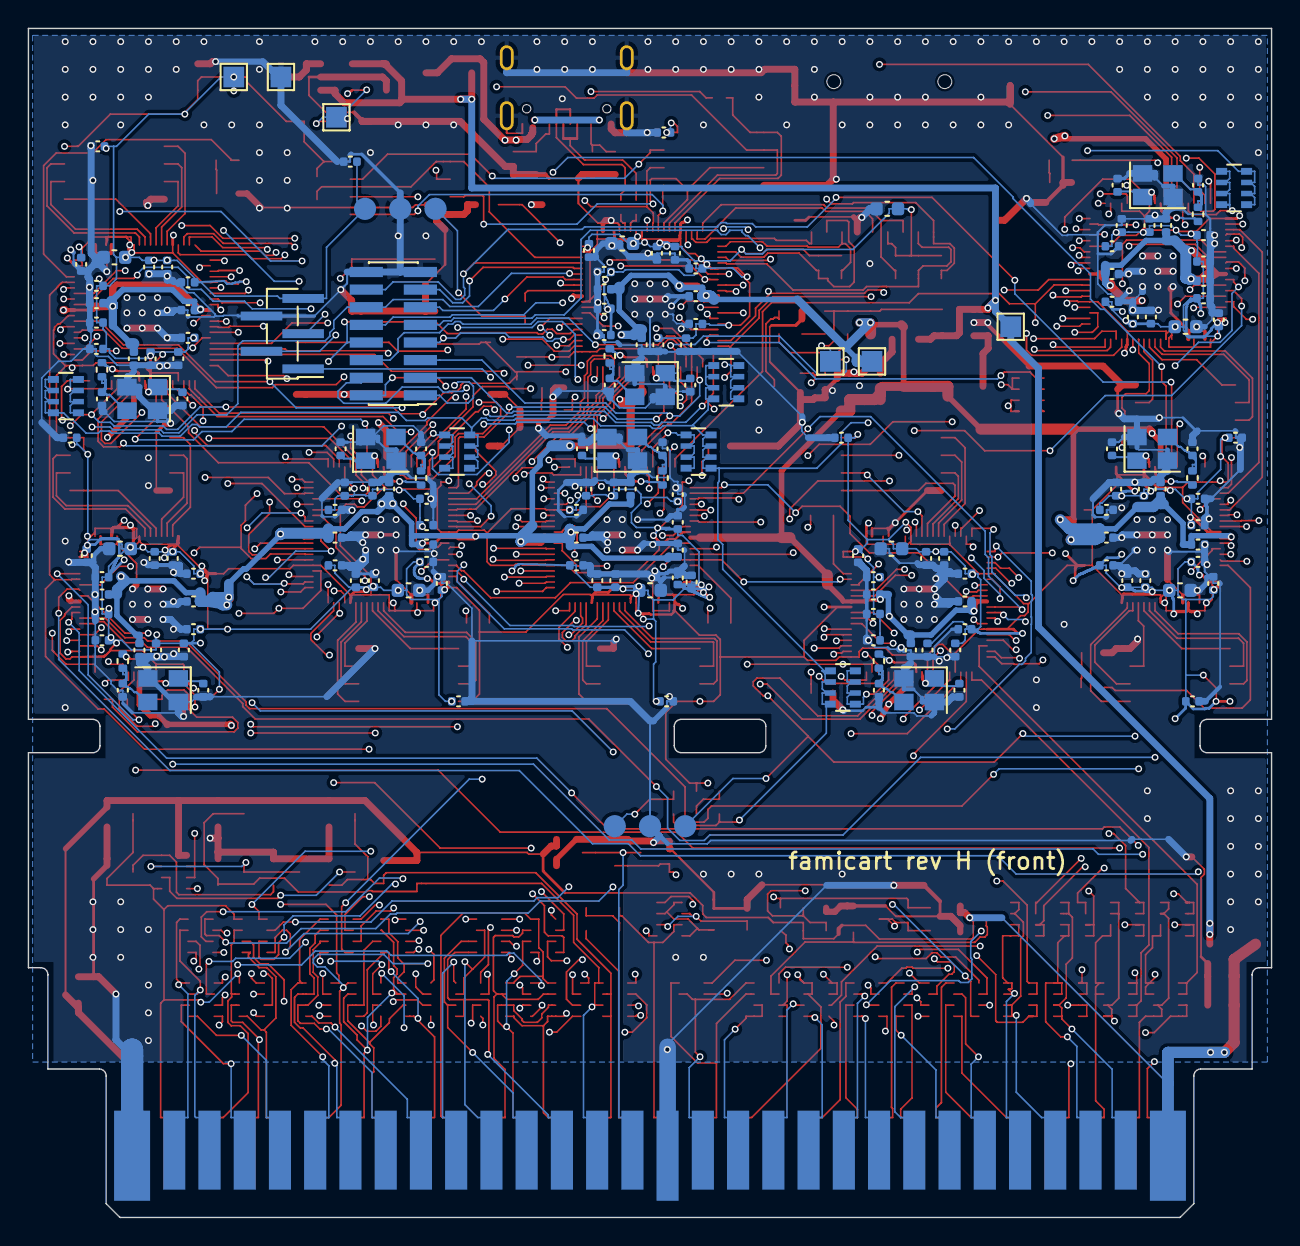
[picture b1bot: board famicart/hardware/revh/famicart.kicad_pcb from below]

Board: 6 copper layers, 89.6 x 85.7 mm, 307 parts (170 on the bottom side), 364 nets.

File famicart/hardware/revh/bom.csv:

Qty,Value,Footprint,References,Suggested part
1,Famicom 60-pin edge,Famicom_CardEdge_60_M,J1,"PCB card edge (gold fingers), no part"
8,RP2350B,QFN-80-1EP_10x10mm_P0.4mm_EP3.4x3.4mm_NoVia,U1 U2 U3 U4 U5 U6 U8 U9,"RP2350B QFN-80 (LCSC C42415655, JLCPCB Extended)"
9,W25Q128JVSIQ,SOIC-8_5.23x5.23mm_P1.27mm,U7 U11 U12 U13 U14 U15 U16 U18 U19,"W25Q128JVSIQ 16MB SPI flash SOIC-8 208mil (LCSC C97521, JLCPCB Basic)"
113,100n,C_0402_1005Metric,C1 C2 C5 C6 C7 C9 C10 C11 C12 C13 C14 C16 C17 C18 C21 C22 C23 C24 C25 C26 C27 C28 C29 C30 C31 C33 C34 C35 C38 C39 C40 C41 C42 C43 C44 C45 C46 C47 C48 C50 C51 C52 C55 C56 C57 C58 C59 C60 C61 C62 C63 C64 C65 C67 C68 C69 C72 C73 C74 C75 C76 C77 C78 C79 C80 C81 C82 C84 C85 C86 C89 C90 C91 C92 C93 C94 C95 C96 C97 C98 C99 C101 C102 C103 C106 C107 C108 C109 C110 C111 C112 C113 C114 C115 C116 C118 C119 C120 C123 C124 C125 C126 C127 C128 C129 C130 C131 C132 C133 C135 C136 C137 C148,"CL05B104KO5NNNC 100nF 0402 (LCSC C1525, JLCPCB Basic)"
9,4.7u,C_0603_1608Metric,C15 C32 C49 C66 C83 C100 C117 C134 C147,"CL10A475KO8NNNC 4.7uF 0603 (LCSC C19666, JLCPCB Basic)"
8,12MHz,Crystal_SMD_3225-4Pin_3.2x2.5mm,Y1 Y2 Y3 Y4 Y5 Y6 Y8 Y9,"TXM12M0004322CBCDO00T 12MHz 9pF 3225 (LCSC C362368, JLCPCB Extended)"
16,12p,C_0402_1005Metric,C19 C20 C36 C37 C53 C54 C70 C71 C87 C88 C104 C105 C121 C122 C138 C139,"0402CG120J500NT 12pF C0G 0402 (LCSC C1547, JLCPCB Basic)"
9,1k,R_0402_1005Metric,R1 R3 R5 R7 R9 R11 R13 R15 R52,"0402WGF1001TCE 1k 0402 (LCSC C11702, JLCPCB Basic)"
8,KT-0603R,LED_0603_1608Metric,D21 D22 D23 D24 D25 D26 D28 D29,"KT-0603R red LED 0603 (LCSC C2286, JLCPCB Basic)"
21,2.2k,R_0603_1608Metric,R2 R4 R6 R8 R10 R12 R14 R16 R17 R19 R20 R21 R22 R23 R24 R28 R29 R32 R37 R51 R54,"0603WAF2201T5E 2.2k 0603 (LCSC C4190, JLCPCB Basic)"
24,1k x4,R_Array_Convex_4x0603,RN1 RN2 RN3 RN4 RN7 RN8 RN9 RN10 RN17 RN18 RN19 RN20 RN21 RN22 RN23 RN24 RN25 RN26 RN31 RN32 ZA1 ZA2 ZA3 ZA4,"4D03WGJ0102T5E 1k x4 0603 (LCSC C20197, JLCPCB Basic)"
14,680 x4,R_Array_Convex_4x0603,RN5 RN6 RN11 RN12 RN13 RN14 RN15 RN16 RN27 RN28 RN29 RN30 ZD1 ZD2,"4D03WGJ0681T5E 680R x4 0603 (LCSC C12035, JLCPCB Extended)"
7,2N7002,SOT-23,Q1 Q2 Q3 Q4 Q5 Q6 Q7,"2N7002 SOT-23 (LCSC C8545, JLCPCB Basic)"
8,100k,R_0603_1608Metric,R18 R33 R34 R35 R46 R48 R49 R50,"0603WAF1003T5E 100k 0603 (LCSC C25803, JLCPCB Basic)"
5,BAV99,SOT-23,D5 D6 D7 D8 D9,"BAV99,215 SOT-23 (LCSC C2500, JLCPCB Basic)"
2,10n,C_0603_1608Metric,C140 C141,"0603B103K500NT 10nF 0603 (LCSC C57112, JLCPCB Basic)"
14,10k,R_0603_1608Metric,R25 R26 R27 R30 R31 R36 R40 R41 R42 R43 R44 R45 R47 R53,"0603WAF1002T5E 10k 0603 (LCSC C25804, JLCPCB Basic)"
6,10u,C_0805_2012Metric,C3 C4 C8 C142 C145 C146,"CL21A106KAYNNNE 10uF 0805 (LCSC C15850, JLCPCB Basic)"
2,B5819W,D_SOD-123,D10 D11,"B5819W SOD-123 (LCSC C8598, JLCPCB Basic)"
2,TLV62569DBVR,SOT-23-5,U20 U21,"TLV62569DBVR 2A buck SOT-23-5 (LCSC C141836, JLCPCB Extended)"
2,2.2uH,L_SXN_SMNR4020,L1 L2,"SMNR4020-2.2UH 2.2uH 4x4 (LCSC C135262, JLCPCB Extended)"
2,22u,C_0805_2012Metric,C143 C144,"CL21A226MAQNNNE 22uF 0805 (LCSC C45783, JLCPCB Basic)"
1,TP +1V1,TestPoint_Pad_1.5x1.5mm,TP1,
1,TP +3V3,TestPoint_Pad_1.5x1.5mm,TP2,
1,TP V5_IN,TestPoint_Pad_1.5x1.5mm,TP3,
1,TP FB_3V3,TestPoint_Pad_1.5x1.5mm,TP4,
1,TP FB_1V1,TestPoint_Pad_1.5x1.5mm,TP5,
1,TP GND,TestPoint_Pad_1.5x1.5mm,TP6,
1,TYPE-C-31-M-12,USB_C_Receptacle_HRO_TYPE-C-31-M-12_JLC,J7,"HRO TYPE-C-31-M-12 USB-C (LCSC C165948, JLCPCB Extended)"
2,27,R_0402_1005Metric,R38 R39,"0402WGF270JTCE 27R 0402 (LCSC C25100, JLCPCB Extended)"
1,TF-01A,microSD_HRO_TF-01A,J3,"HRO TF-01A microSD (LCSC C91145, JLCPCB Extended)"
3,TS-1187A,SW_Push_1P1T_XKB_TS-1187A,SW1 SW2 SW3,"TS-1187A-B-A-B (LCSC C318884, JLCPCB Basic)"
1,RST/GND/LINK pads,WirePads_1x3,J2,
1,EXT/GND/3V3 pads,WirePads_1x3,J4,
1,hub SWD pads,PinHeader_1x05_P1.27mm_Vertical_SMD_Pin1Left,J5,
1,SWD pads U1-U5 U8 U9,PinHeader_2x08_P1.27mm_Vertical_SMD,J6,
